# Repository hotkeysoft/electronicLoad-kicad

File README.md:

# Electronic Load
Rev A July 2021

***Work in progress, do not use***

- USB Powered (USB-B Connector)
- 0-24V DC Input
- Adjustable current range: 0-4A
- I2C OLED 0.96" Display
- Rotary Encoder w/switch
- Temperature Sensors w/hardware shutdown
- 5V Cooling fan (PWM Speed Control)

Images
============
|Front                                                 | Back                                              |
|------------------------------------------------------|---------------------------------------------------|
|||

### Schematics (pdf)
- [Complete schematics](./img/schema.pdf)

### PCB Images (svg)
- [Top](./img/pcb-front.svg)
- [GND Plane](./img/pcb-in1.svg)
- [VCC Plane](./img/pcb-in2.svg)
- [Bottom](./img/pcb-back.svg)

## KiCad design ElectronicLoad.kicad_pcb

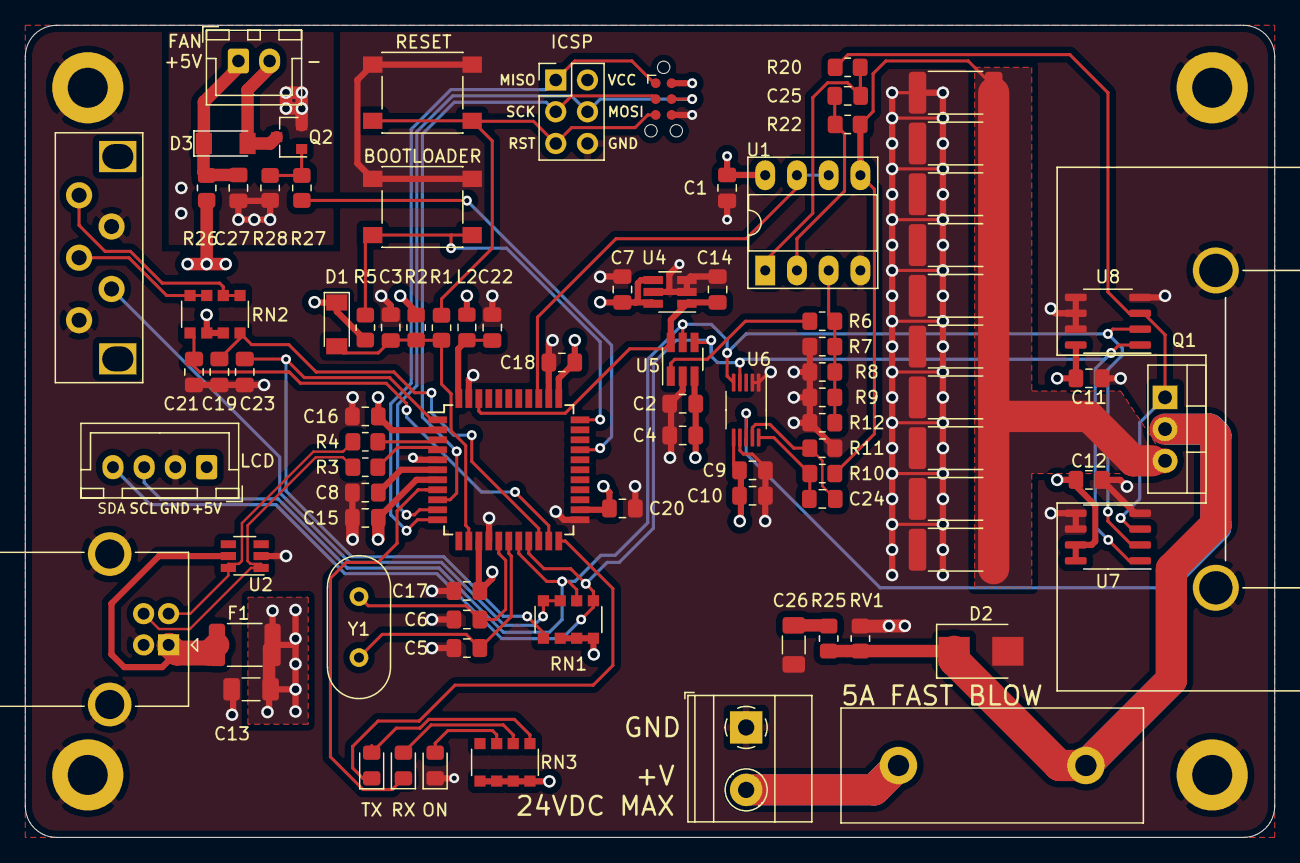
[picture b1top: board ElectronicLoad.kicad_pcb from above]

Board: 4 copper layers, 100.0 x 65.0 mm, 93 parts (0 on the bottom side), 47 nets.

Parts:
C1, C2, C3, C7, C9, C11, C12, C15, C16, C17, C18, C20, C22, C24: 100nF; C_0805_2012Metric_Pad1.18x1.45mm_HandSolder
C4, C8, C10, C27: 1μF; C_0805_2012Metric_Pad1.18x1.45mm_HandSolder
C5, C6: 18pF; C_0805_2012Metric_Pad1.18x1.45mm_HandSolder
C13, C26: 2.2μF; C_1206_3216Metric_Pad1.33x1.80mm_HandSolder
C14: 300pF; C_0805_2012Metric_Pad1.18x1.45mm_HandSolder
C19, C21, C23: 10nF; C_0805_2012Metric_Pad1.18x1.45mm_HandSolder
C25: 22nF; C_0805_2012Metric_Pad1.18x1.45mm_HandSolder
D1, D3: L4148; D_MiniMELF
D2: SK520BTR; D_SMB
F1: 500mA; Fuse_1812_4532Metric_Pad1.30x3.40mm_HandSolder
F2: 5A Fast; Fuse_PTF-76
FAN1: 5V; JST_XH_B2B-XH-A_1x02_P2.50mm_Vertical
H1, H2, H3, H4: MountingHole_Pad; MountingHole_3.2mm_M3_ISO7380_Pad
HS1: Heatsink; HSINK_6396BG
J1: USB_B; USB_B_OST_USB-B1HSxx_Horizontal
J2: TagConnect; Tag-Connect_TC2030-IDC-NL_2x03_P1.27mm_Vertical
J3: ICSP; PinHeader_2x03_P2.54mm_Vertical
J4: Load; TerminalBlock_Phoenix_MKDS-1,5-2_1x02_P5.00mm_Horizontal
L2: 10μH; L_0805_2012Metric_Pad1.15x1.40mm_HandSolder
LCD1: OLED 128x64 I2C; JST_XH_B4B-XH-A_1x04_P2.50mm_Vertical
LED1: TX; LED_0805_2012Metric_Pad1.15x1.40mm_HandSolder
LED2: RX; LED_0805_2012Metric_Pad1.15x1.40mm_HandSolder
LED3: POWER; LED_0805_2012Metric_Pad1.15x1.40mm_HandSolder
Q1: MTP3055VL; TO-220-3_Vertical
Q2: DMG2302U; SOT-23
R1: 330R; R_0805_2012Metric_Pad1.20x1.40mm_HandSolder
R2: 4.7K; R_0805_2012Metric_Pad1.20x1.40mm_HandSolder
R3, R4: 22R; R_0805_2012Metric_Pad1.20x1.40mm_HandSolder
R5, R6, R7, R8, R9, R12, R28: 10K; R_0805_2012Metric_Pad1.20x1.40mm_HandSolder
R10, R11, R27: 100R; R_0805_2012Metric_Pad1.20x1.40mm_HandSolder
R13, R14, R15, R16, R17, R18, R19, R21, R23, R24: 1R; R_2512_6332Metric_Pad1.40x3.35mm_HandSolder
R20: 470R; R_0805_2012Metric_Pad1.20x1.40mm_HandSolder
R22: 1K; R_0805_2012Metric_Pad1.20x1.40mm_HandSolder
R25: 2R2; R_0805_2012Metric_Pad1.20x1.40mm_HandSolder
R26: 1R; R_0805_2012Metric_Pad1.20x1.40mm_HandSolder
RN1, RN2: 10K; R_Array_Convex_4x1206
RN3: 1K; R_Array_Convex_4x1206
RV1: VC0805K121R020; R_0805_2012Metric_Pad1.20x1.40mm_HandSolder
SW1: RESET; SW_SPST_PTS645
SW2: BOOTLOADER; SW_SPST_PTS645
SW3: Control; RotaryEncoder_Bourns_PEC16-2xxxF-Sxxxx
U1: TLC272; DIP-8_W7.62mm_Socket_LongPads
U2: NUP2114; TSOT-23-6
U3: ATmega32U4-AU; TQFP-44_10x10mm_P0.8mm
U4: MCP1501-20; SOT-23-6_Handsoldering
U5: MCP4726A3T; SOT-23-6_Handsoldering
U6: INA220; VSSOP-10_3x3mm_P0.5mm
U7, U8: PCT2075D; SO-8_3.9x4.9mm_P1.27mm
Y1: 16MHz; Crystal_HC49-4H_Vertical

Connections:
/D_AVR+: R3.2, U3.4
/D_AVR-: R4.2, U3.3
/D_USB+: J1.3, R3.1, U2.1
/D_USB-: J1.2, R4.1, U2.6
/FAN-: D3.2, FAN1.2, Q2.3
/ILOAD+: Q1.3, R10.2, R13.1, R14.1, R15.1, R16.1, R17.1, R18.1, R19.1, R21.1, R22.1, R23.1, R24.1, U1.5
/ISET: R6.2, U5.1
/ISET_DIV5: R6.1, R7.1, R8.2, R9.2, R12.2, U1.3
/LOAD: F2.1, J4.2
/MISO: J2.1, J3.1, U3.11
/MOSI: J2.4, J3.4, U3.10
/SCK: J2.3, J3.3, U3.9
/UCAP: C8.1, U3.6
/VBUS: F1.2, J1.1, U2.5
/Vin+: C24.1, R10.1, U6.10
/Vin-: C24.2, R11.1, U6.9
/XTAL1: C5.2, U3.17, Y1.1
/XTAL2: C6.2, U3.16, Y1.2
/~HWB: R5.2, SW2.1, U3.33
/~RESET: C3.1, D1.2, R1.1, R2.2, U3.13
AVCC: C22.1, L2.2, U3.44
FAN_PWM: R27.1, U3.30
FAN_VCC: C27.1, D3.1, FAN1.1, R26.2
GND: C1.2, C2.2, C3.2, C4.2, C5.1, C6.1, C7.2, C8.2, C9.2, C10.2, C11.2, C12.2, C13.2, C14.2, C15.2, C16.2, C17.2, C18.2, C19.2, C20.2, C21.2, C22.2, C23.2, C26.2, C27.2, D2.2, H1.1, H2.1, H3.1, H4.1, HS1.1, HS1.2, J1.4, J1.5, J2.6, J3.6, J4.1, LCD1.2, LED3.1, Q2.2, R7.2, R8.1, R9.1, R11.2, R12.1, R13.2, R14.2, R15.2, R16.2, R17.2, R18.2, R19.2, R21.2, R23.2, R24.2, R28.2, RV1.2, SW1.1, SW2.2, SW3.C, SW3.S1, U1.4, U2.2, U3.5, U3.15, U3.23, U3.35, U3.43, U4.2, U4.3, U4.5, U5.2, U6.1, U6.2, U6.7, U7.4, U7.5, U7.6, U8.4, U8.5, U8.6, U8.7
ILOAD_MCU: U1.6, U1.7, U3.36
unnamed: C25.1, R20.2, U1.1
unnamed: C25.2, R22.2, U1.2
unnamed: C26.1, R25.2
unnamed: LED1.2, RN3.5
unnamed: LED2.2, RN3.6
unnamed: LED3.2, RN3.7
unnamed: Q2.1, R27.2, R28.1
unnamed: RN1.3, RN1.4, SW3.S2
unnamed: RN2.1, RN2.2, SW3.A
unnamed: RN2.3, RN2.4, SW3.B
ROT_A: C19.1, RN2.8, U3.20
ROT_B: C21.1, RN2.5, U3.21
ROT_SW: C23.1, RN1.5, U3.1
SCL: LCD1.3, RN1.2, U3.18, U5.5, U6.5, U7.2, U8.2
SDA: LCD1.4, RN1.1, U3.19, U5.4, U6.4, U7.1, U8.1
VCC: C1.1, C2.1, C4.1, C7.1, C9.1, C10.1, C11.1, C12.1, C13.1, C15.1, C16.1, C17.1, C18.1, C20.1, D1.1, F1.1, J2.2, J3.2, L2.1, LCD1.1, R2.1, R5.1, R26.1, RN1.6, RN1.7, RN1.8, RN2.6, RN2.7, RN3.1, RN3.2, RN3.3, RN3.4, U1.8, U3.2, U3.7, U3.14, U3.24, U3.34, U4.4, U4.6, U5.3, U6.6, U7.7, U7.8, U8.8
VLOAD: D2.1, F2.2, Q1.2, R25.1, RV1.1, U6.8
VREF2048: C14.1, U3.42, U4.1, U5.6
~EXT_RESET: J2.5, J3.5, R1.2, SW1.2
~OT_SHUTDOWN: Q1.1, R20.1, U7.3, U8.3
~RXLED: LED2.1, U3.8
~TXLED: LED1.1, U3.22

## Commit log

2021-07-24 Initial import
2021-07-25 USB, MCU
2021-07-25 Fan control
2021-07-26 Power switch, led
2021-07-31 Encoder, layout
2021-08-05 Heatsink, Fan, Layout
2021-08-07 Routing
2021-08-08 Move input connector, routing, silkscreen
2021-08-08 Move FAN_PWM to D10
2021-08-09 Reduced decoupling capacitance on VBUS to <10uF
2021-08-09 Cleanup
2021-08-10 3d model for rotary encoder
2021-08-11 Relabel components
2021-08-11 usbC (wip)
2021-08-13 Move connectors
2021-08-13 Add plot
2021-08-13 Tweak rotary switch footprint
2021-08-13 Added renders
2021-08-13 Added RevA Fab
